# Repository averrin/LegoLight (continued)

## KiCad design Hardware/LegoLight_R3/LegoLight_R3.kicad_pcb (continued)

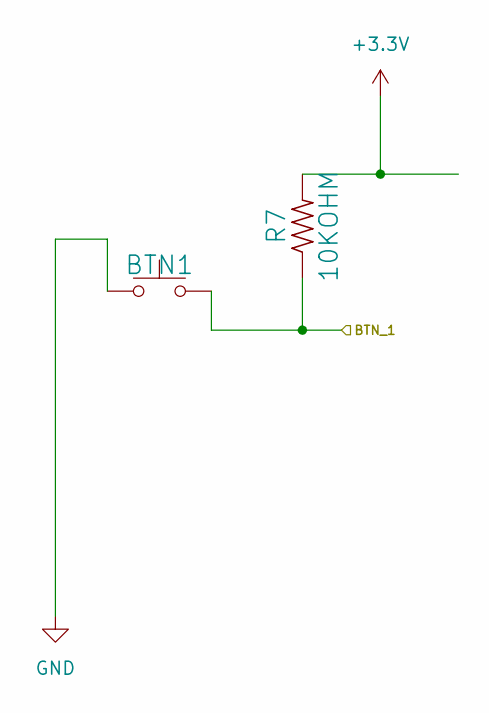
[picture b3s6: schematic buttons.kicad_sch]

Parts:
BTN1: BTN; B3U-1000P; PARTREV C; Mouser Part Number 653-B3U-1000P
R7: 10KOHM; R_0805_2012Metric_Pad1.20x1.40mm_HandSolder; Mouser Part Number 652-CR0805-JW-103ELF

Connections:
+3.3V: R7.2; also elsewhere on the board
/PA11: BTN1.2, R7.1; also elsewhere on the board
GND: BTN1.1; also elsewhere on the board

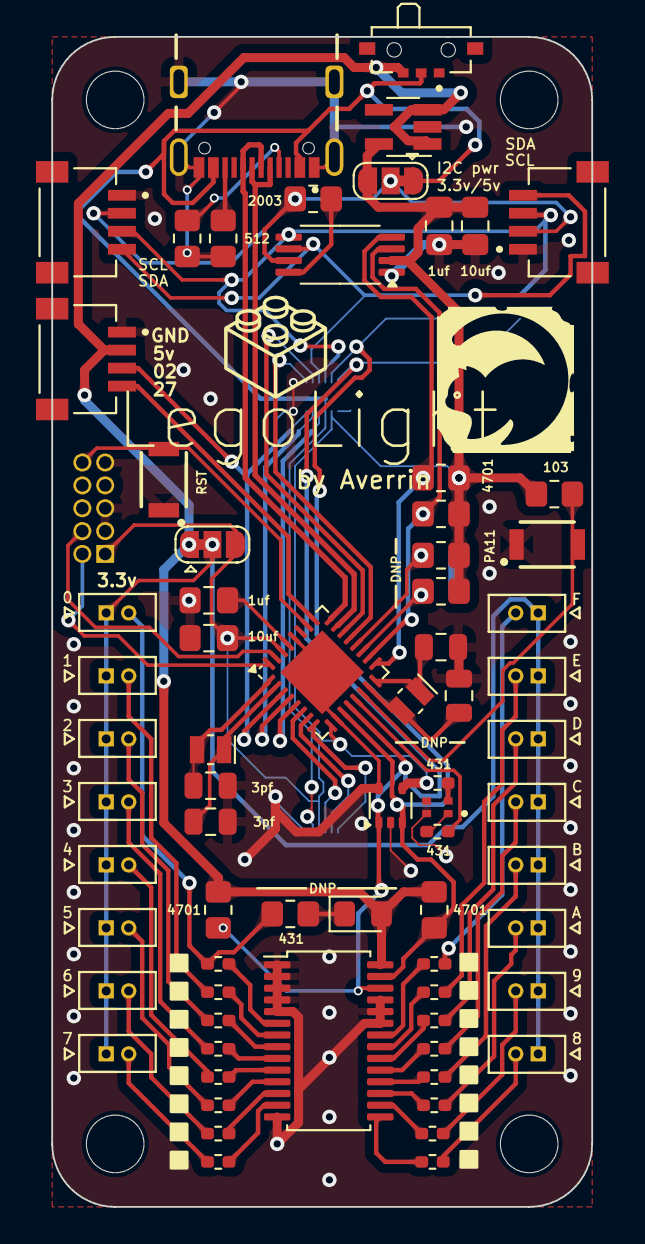
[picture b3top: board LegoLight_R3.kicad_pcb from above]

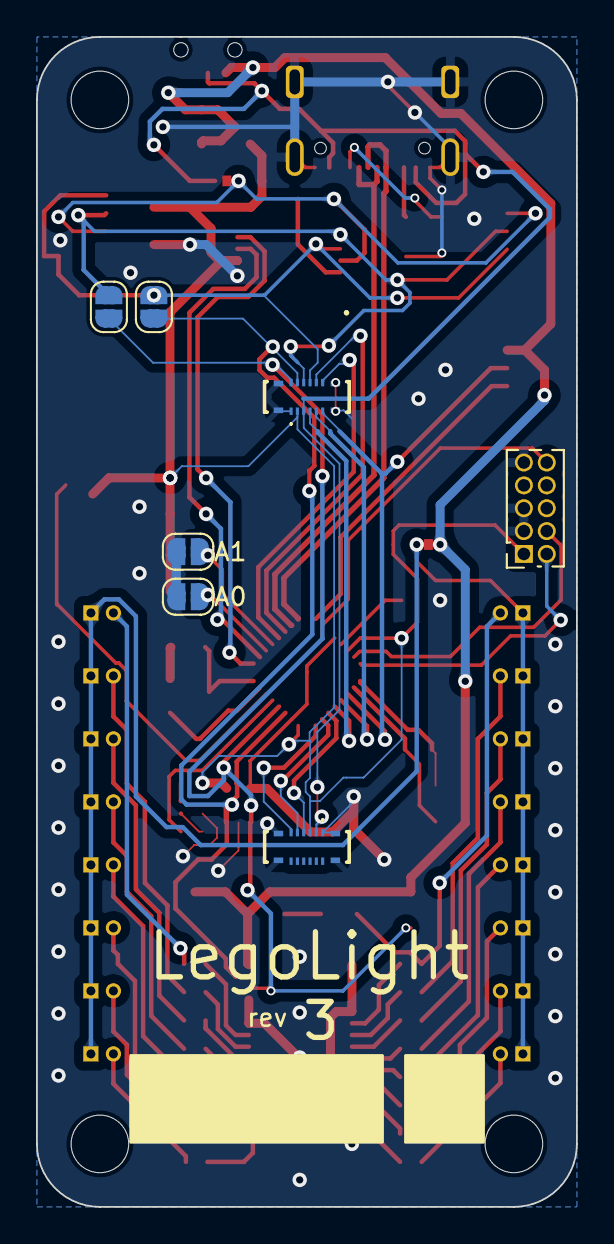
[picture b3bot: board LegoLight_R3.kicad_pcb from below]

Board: 2 copper layers, 30.0 x 65.0 mm, 82 parts (7 on the bottom side), 73 nets.

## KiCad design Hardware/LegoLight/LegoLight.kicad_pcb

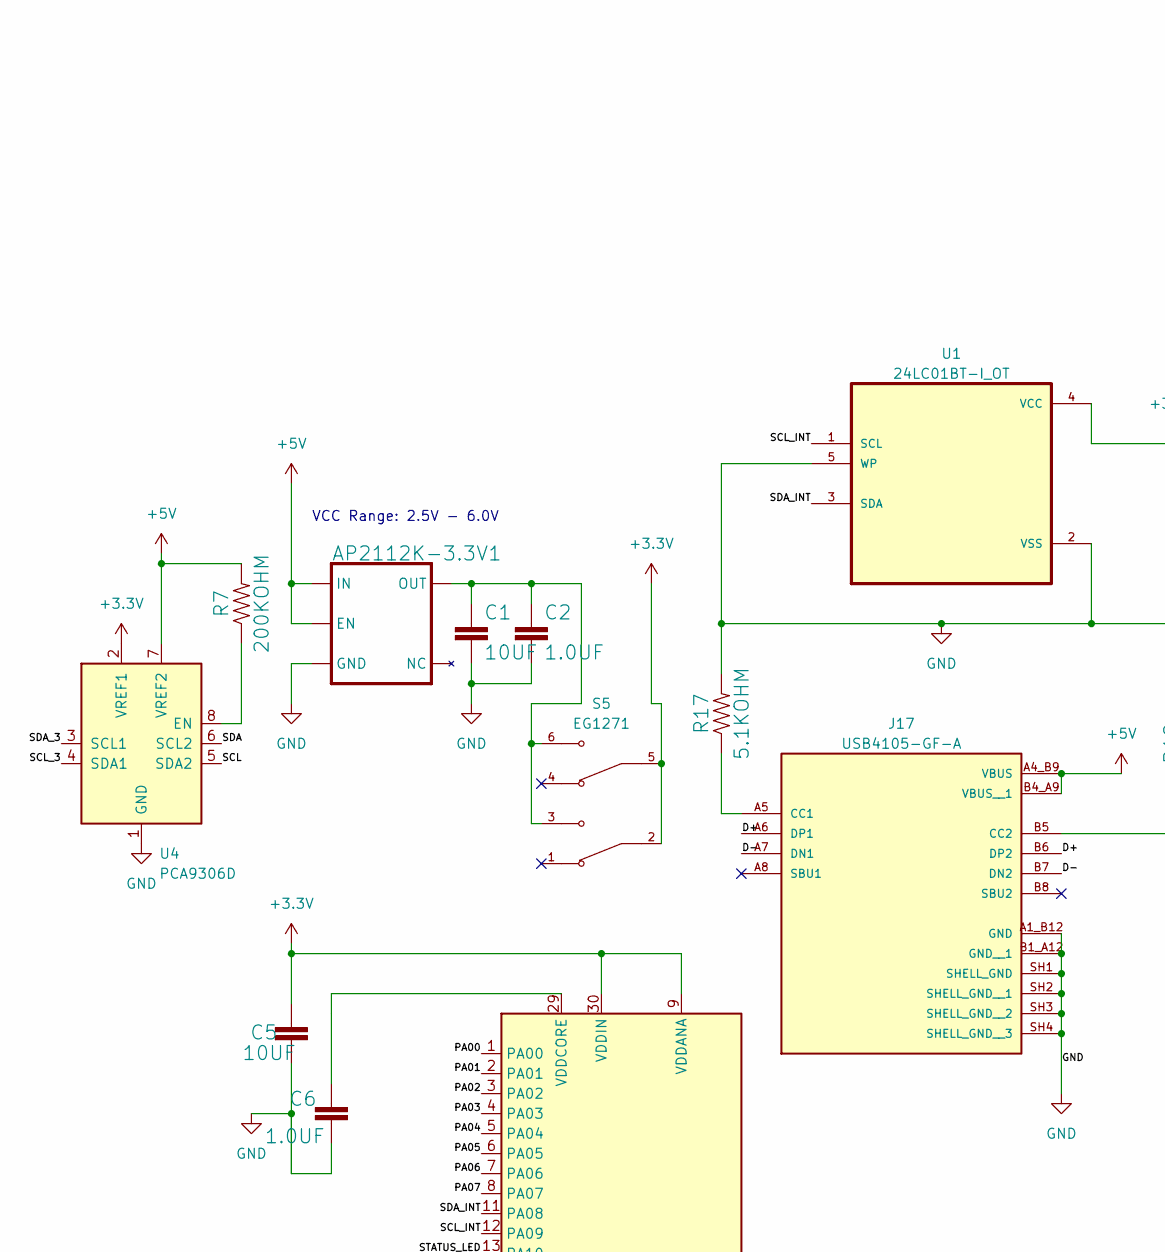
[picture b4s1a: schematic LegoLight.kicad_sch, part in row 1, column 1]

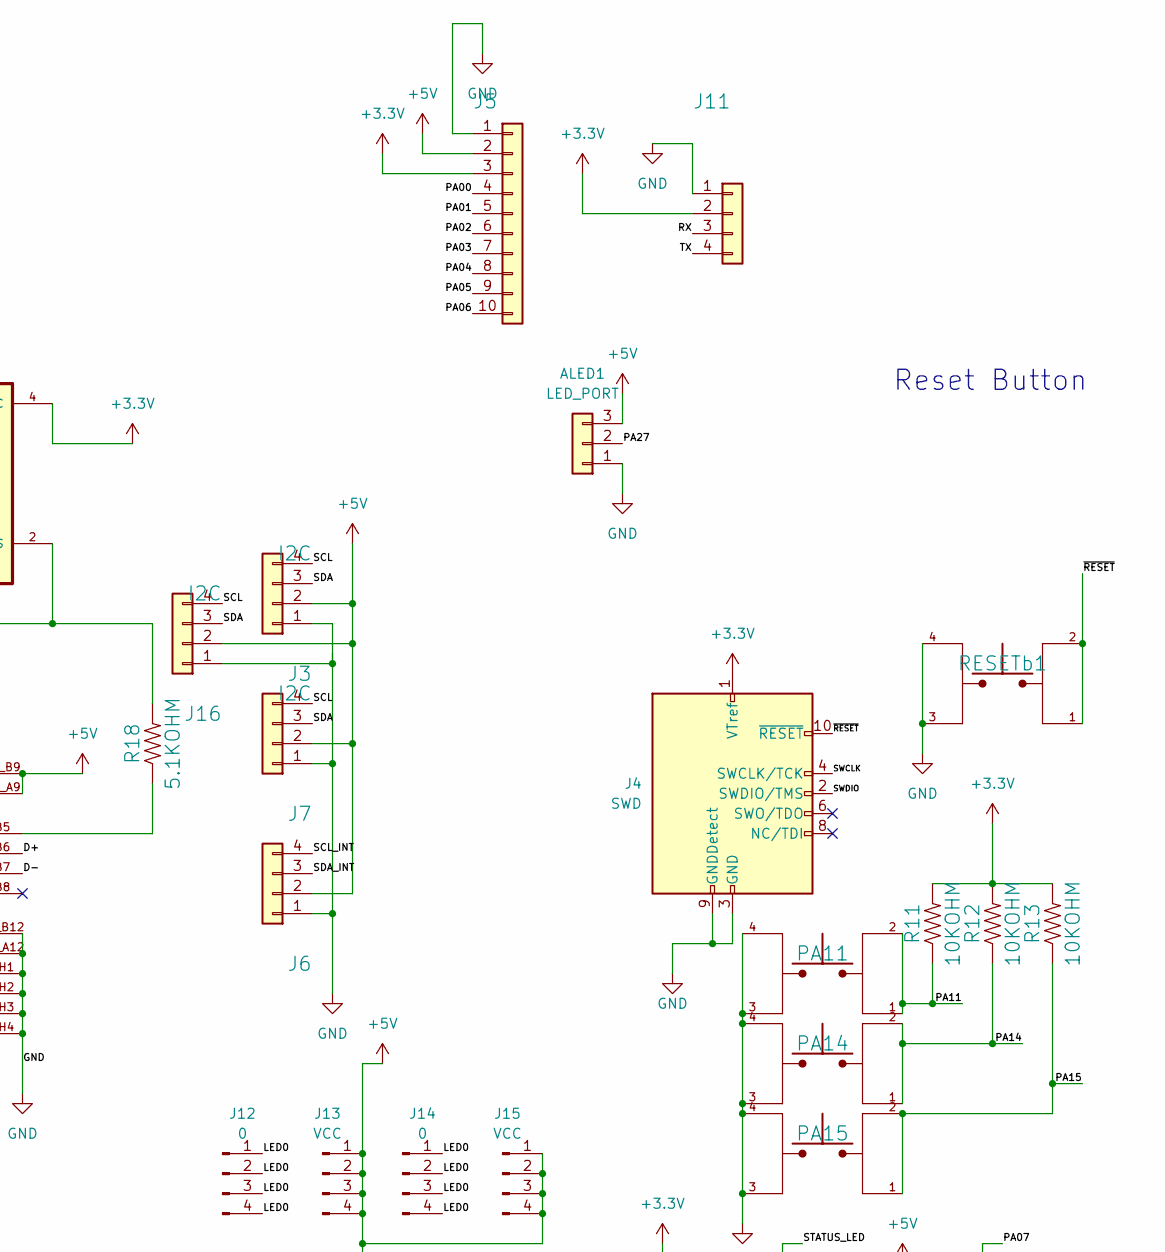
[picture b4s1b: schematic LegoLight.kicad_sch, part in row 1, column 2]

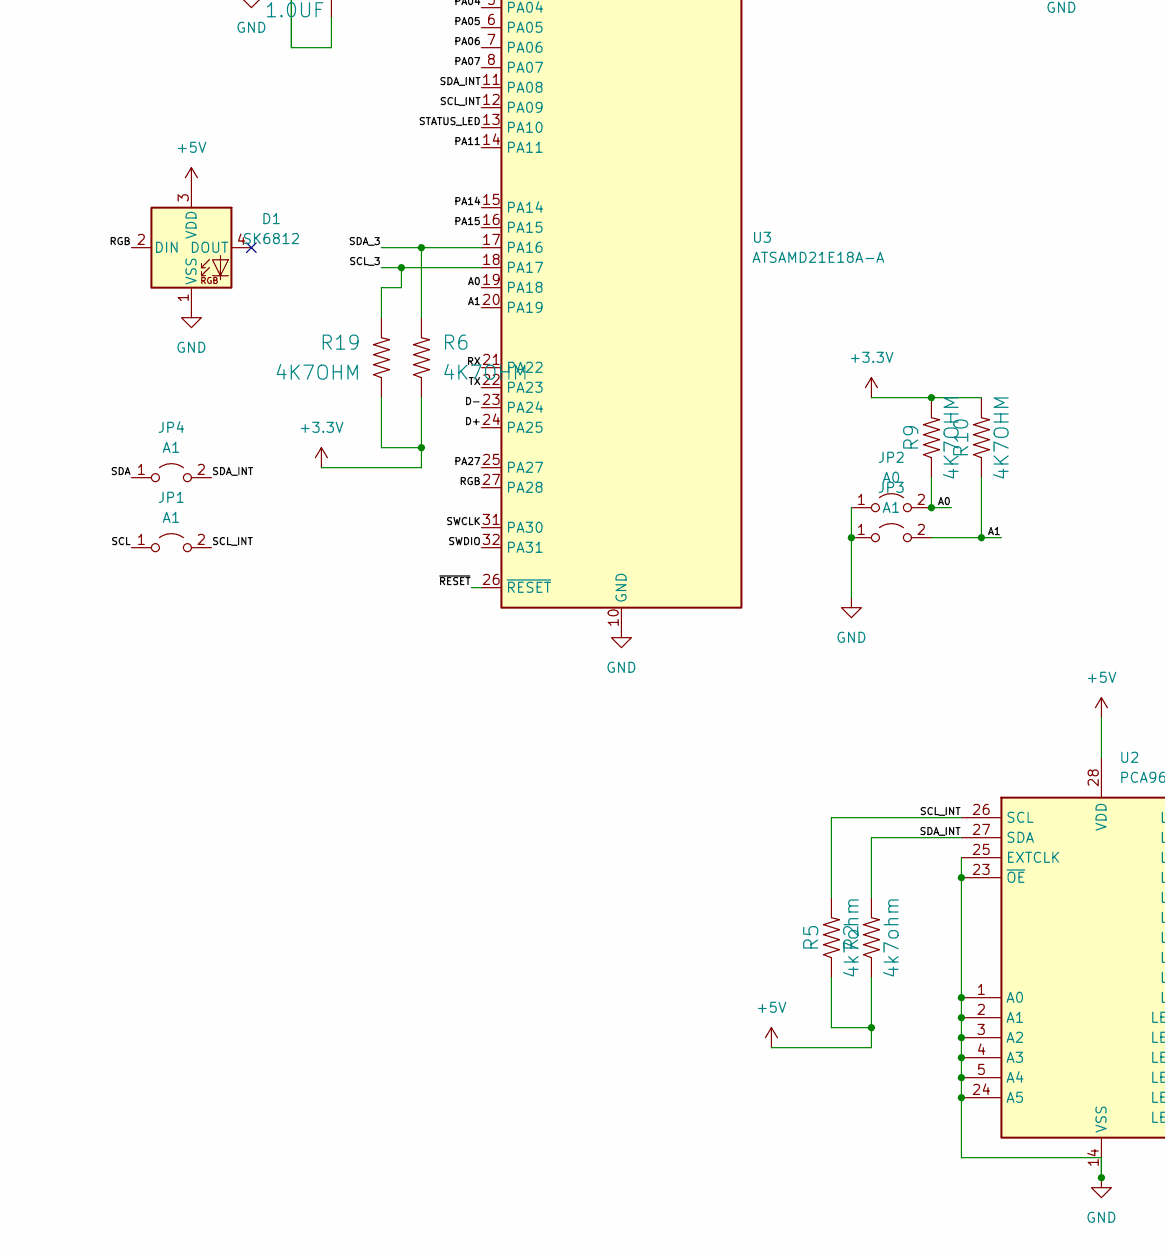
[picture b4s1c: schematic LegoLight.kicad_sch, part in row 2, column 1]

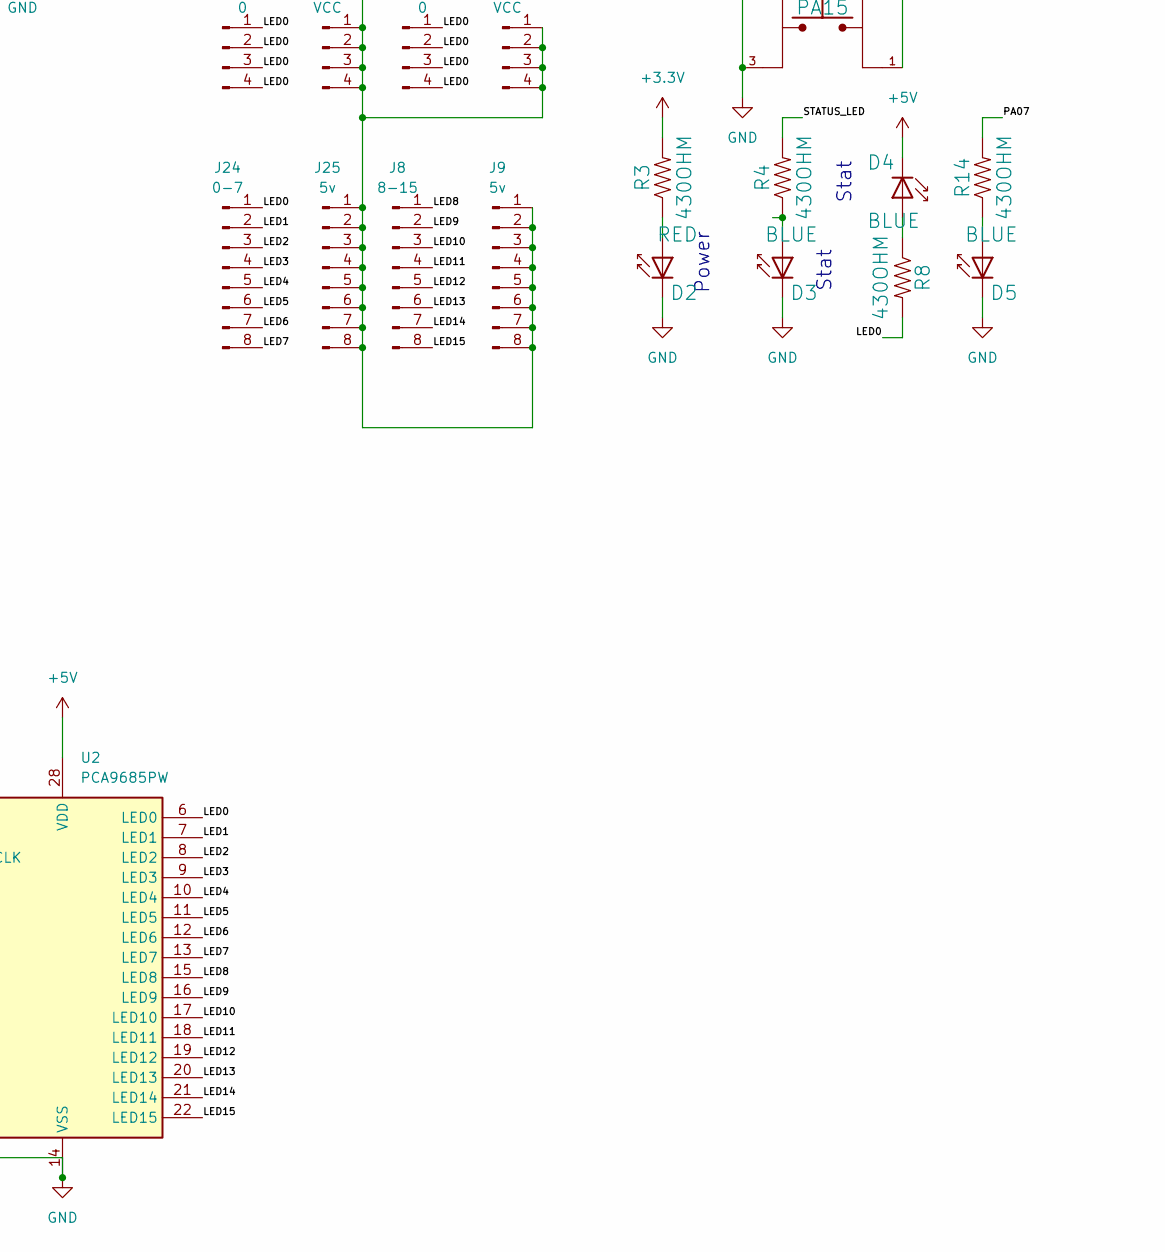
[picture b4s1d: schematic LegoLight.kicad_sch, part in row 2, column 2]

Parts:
ALED1: LED_PORT; PinHeader_1x03_P2.54mm_Vertical
AP2112K-3.3V1: AP2112K-3.3V; SOT-23-5_HandSoldering
C1, C5: 10UF; C_1206_3216Metric_Pad1.33x1.80mm_HandSolder
C2, C6: 1.0UF; C_1206_3216Metric_Pad1.33x1.80mm_HandSolder
D1: SK6812; LED_SK6812_PLCC4_5.0x5.0mm_P3.2mm
D2: RED; LED_1206_3216Metric_Pad1.42x1.75mm_HandSolder
D3, D4, D5: BLUE; LED_1206_3216Metric_Pad1.42x1.75mm_HandSolder
J3, J7: I2C; NS-Tech_Grove_1x04_P2mm_Vertical
J4: SWD; PinSocket_2x05_P1.27mm_Vertical
J5: C1; PinHeader_1x10_P2.54mm_Vertical
J6: I2C_INT; PinHeader_1x04_P2.54mm_Vertical
J8: 8-15; PinHeader_1x08_P2.54mm_Vertical
J9, J25: 5v; PinHeader_1x08_P2.54mm_Vertical
J11: C0; PinHeader_1x04_P2.54mm_Vertical
J12, J14: 0; PinHeader_1x04_P2.54mm_Vertical
J13, J15: VCC; PinHeader_1x04_P2.54mm_Vertical
J16: I2C; PinHeader_1x04_P2.54mm_Vertical
J17: USB4105-GF-A; GCT_USB4105-GF-A; PARTREV B3
J24: 0-7; PinHeader_1x08_P2.54mm_Vertical
JP1, JP3, JP4: A1; SolderJumper-2_P1.3mm_Open_RoundedPad1.0x1.5mm
JP2: A0; SolderJumper-2_P1.3mm_Open_RoundedPad1.0x1.5mm
PA11, PA14, PA15: MOMENTARY-SWITCH-SPST-SMD-4.6X2.8MM; SW_TL3305AF160QG; PARTREV C
R2, R5: 4k7ohm; R_1206_3216Metric_Pad1.30x1.75mm_HandSolder
R3, R4, R8, R14: 430OHM; R_1206_3216Metric_Pad1.30x1.75mm_HandSolder
R6, R9, R10, R19: 4K7OHM; R_1206_3216Metric_Pad1.30x1.75mm_HandSolder
R7: 200KOHM; R_1206_3216Metric_Pad1.30x1.75mm_HandSolder
R11, R12, R13: 10KOHM; R_1206_3216Metric_Pad1.30x1.75mm_HandSolder
R17, R18: 5.1KOHM; R_1206_3216Metric_Pad1.30x1.75mm_HandSolder
RESETb1: TL3305AF160QG; SW_TL3305AF160QG; PARTREV C
S5: EG1271; SW_EG1271; PARTREV G
U1: 24LC01BT-I_OT; SOT95P280X145-5N
U2: PCA9685PW; TSSOP-28_4.4x9.7mm_P0.65mm
U3: ATSAMD21E18A-A; TQFP-32_7x7mm_P0.8mm
U4: PCA9306D; SO-8_3.9x4.9mm_P1.27mm

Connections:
+3.3V: C5.1, J4.1 (VTref), J5.3, J11.2, R3.2, R6.1, R9.2, R10.2, R11.2, R12.2, R13.2, R19.1, S5.2, S5.5, U1.4 (VCC), U3.9 (VDDANA), U3.30 (VDDIN), U4.2 (VREF1)
+5V: ALED1.3, AP2112K-3.3V1.1 (IN), AP2112K-3.3V1.3 (EN), D1.3 (VDD), D4.1 (K), J3.2, J5.2, J6.2, J7.2, J9.1, J9.2, J9.3, J9.4, J9.5, J9.6, J9.7, J9.8, J13.1, J13.2, J13.3, J13.4, J15.1, J15.2, J15.3, J15.4, J16.2, J17.A4_B9 (VBUS), J17.B4_A9 (VBUS__1), J25.1, J25.2, J25.3, J25.4, J25.5, J25.6, J25.7, J25.8, R2.1, R5.1, R7.2, U2.28 (VDD), U4.7 (VREF2)
/A0: JP2.2 (B), R9.1, U3.19 (PA18)
/A1: JP3.2 (B), R10.1, U3.20 (PA19)
/D+: J17.A6 (DP1), J17.B6 (DP2), U3.24 (PA25)
/D-: J17.A7 (DN1), J17.B7 (DN2), U3.23 (PA24)
/LED0: J12.1, J12.2, J12.3, J12.4, J14.1, J14.2, J14.3, J14.4, J24.1, R8.2, U2.6 (LED0)
/LED1: J24.2, U2.7 (LED1)
/LED2: J24.3, U2.8 (LED2)
/LED3: J24.4, U2.9 (LED3)
/LED4: J24.5, U2.10 (LED4)
/LED5: J24.6, U2.11 (LED5)
/LED6: J24.7, U2.12 (LED6)
/LED7: J24.8, U2.13 (LED7)
/LED8: J8.1, U2.15 (LED8)
/LED9: J8.2, U2.16 (LED9)
/LED10: J8.3, U2.17 (LED10)
/LED11: J8.4, U2.18 (LED11)
/LED12: J8.5, U2.19 (LED12)
/LED13: J8.6, U2.20 (LED13)
/LED14: J8.7, U2.21 (LED14)
/LED15: J8.8, U2.22 (LED15)
/PA00: J5.4, U3.1 (PA00)
/PA01: J5.5, U3.2 (PA01)
/PA02: J5.6, U3.3 (PA02)
/PA03: J5.7, U3.4 (PA03)
/PA04: J5.8, U3.5 (PA04)
/PA05: J5.9, U3.6 (PA05)
/PA06: J5.10, U3.7 (PA06)
/PA07: R14.2, U3.8 (PA07)
/PA11: PA11.1, PA11.2, R11.1, U3.14 (PA11)
/PA14: PA14.1, PA14.2, R12.1, U3.15 (PA14)
/PA15: PA15.1, PA15.2, R13.1, U3.16 (PA15)
/PA27: ALED1.2, U3.25 (PA27)
/RGB: D1.2 (DIN), U3.27 (PA28)
/RX: J11.3, U3.21 (PA22)
/SCL: J3.4, J7.4, J16.4, JP1.1 (A), U4.5 (SDA2)
/SCL_3: R19.2, U3.18 (PA17), U4.4 (SDA1)
/SCL_INT: J6.4, JP1.2 (B), R5.2, U1.1 (SCL), U2.26 (SCL), U3.12 (PA09)
/SDA: J3.3, J7.3, J16.3, JP4.1 (A), U4.6 (SCL2)
/SDA_3: R6.2, U3.17 (PA16), U4.3 (SCL1)
/SDA_INT: J6.3, JP4.2 (B), R2.2, U1.3 (SDA), U2.27 (SDA), U3.11 (PA08)
/STATUS_LED: R4.2, U3.13 (PA10)
/SWCLK: J4.4 (SWCLK/TCK), U3.31 (PA30)
/SWDIO: J4.2 (SWDIO/TMS), U3.32 (PA31)
/TX: J11.4, U3.22 (PA23)
/~RESET: J4.10 (~RESET), RESETb1.1, RESETb1.2, U3.26 (~RESET)
GND: ALED1.1, AP2112K-3.3V1.2 (GND), C1.2, C2.2, C5.2, C6.1, D1.1 (VSS), D2.1 (K), D3.1 (K), D5.1 (K), J3.1, J4.3 (GND), J4.5 (GND), J4.9 (GNDDetect), J5.1, J6.1, J7.1, J11.1, J16.1, J17.A1_B12 (GND), J17.B1_A12 (GND__1), J17.SH1 (SHELL_GND), J17.SH2 (SHELL_GND__1), J17.SH3 (SHELL_GND__2), J17.SH4 (SHELL_GND__3), JP2.1 (A), JP3.1 (A), PA11.3, PA11.4, PA14.3, PA14.4, PA15.3, PA15.4, R17.2, R18.2, RESETb1.3, RESETb1.4, U1.2 (VSS), U1.5 (WP), U2.1 (A0), U2.2 (A1), U2.3 (A2), U2.4 (A3), U2.5 (A4), U2.14 (VSS), U2.23 (~OE), U2.24 (A5), U2.25 (EXTCLK), U3.10 (GND), U3.28 (GND), U4.1 (GND)
unnamed: AP2112K-3.3V1.5 (OUT), C1.1, C2.1, S5.3, S5.6
unnamed: D2.2 (A), R3.1
unnamed: D3.2 (A), R4.1
unnamed: D4.2 (A), R8.1
unnamed: D5.2 (A), R14.1
unnamed: J17.A5 (CC1), R17.1
unnamed: J17.B5 (CC2), R18.1
unnamed: C6.2, U3.29 (VDDCORE)
unnamed: R7.1, U4.8 (EN)

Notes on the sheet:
Power
Stat
Reset Button
VCC Range: 2.5V - 6.0V

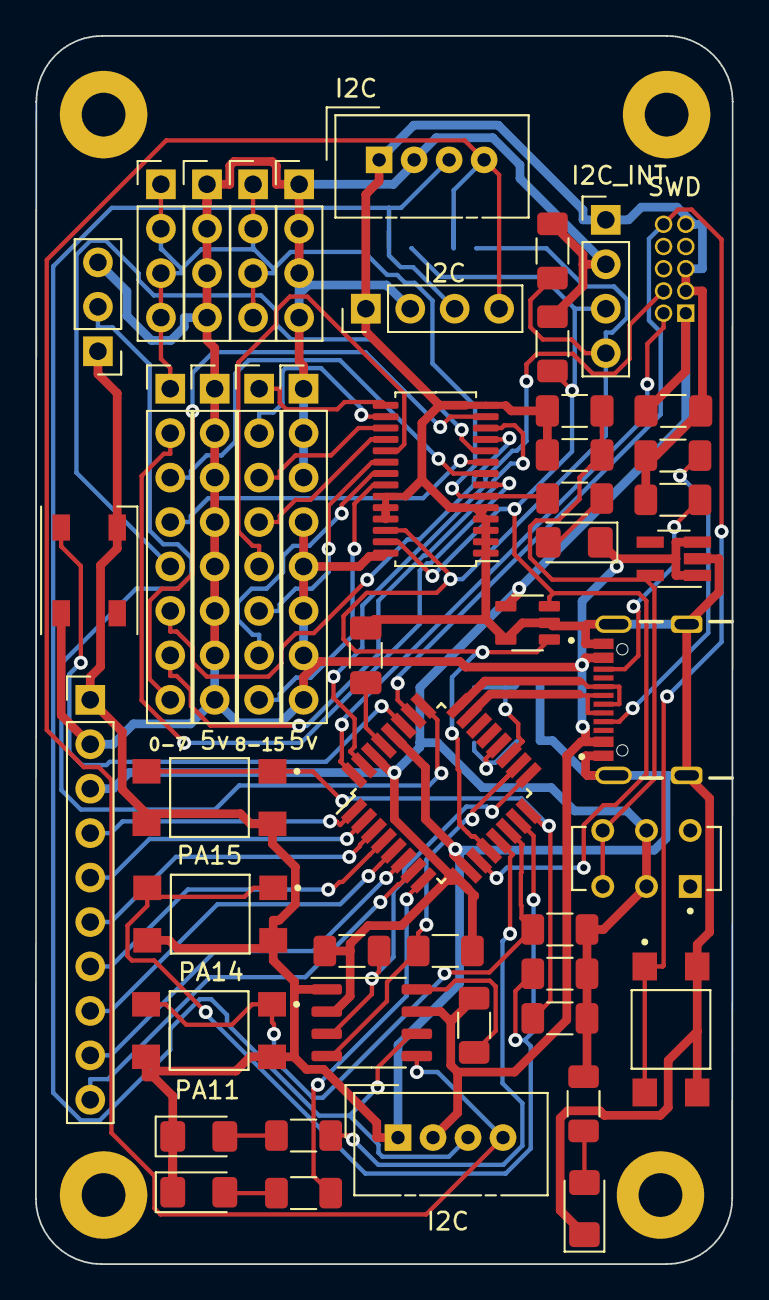
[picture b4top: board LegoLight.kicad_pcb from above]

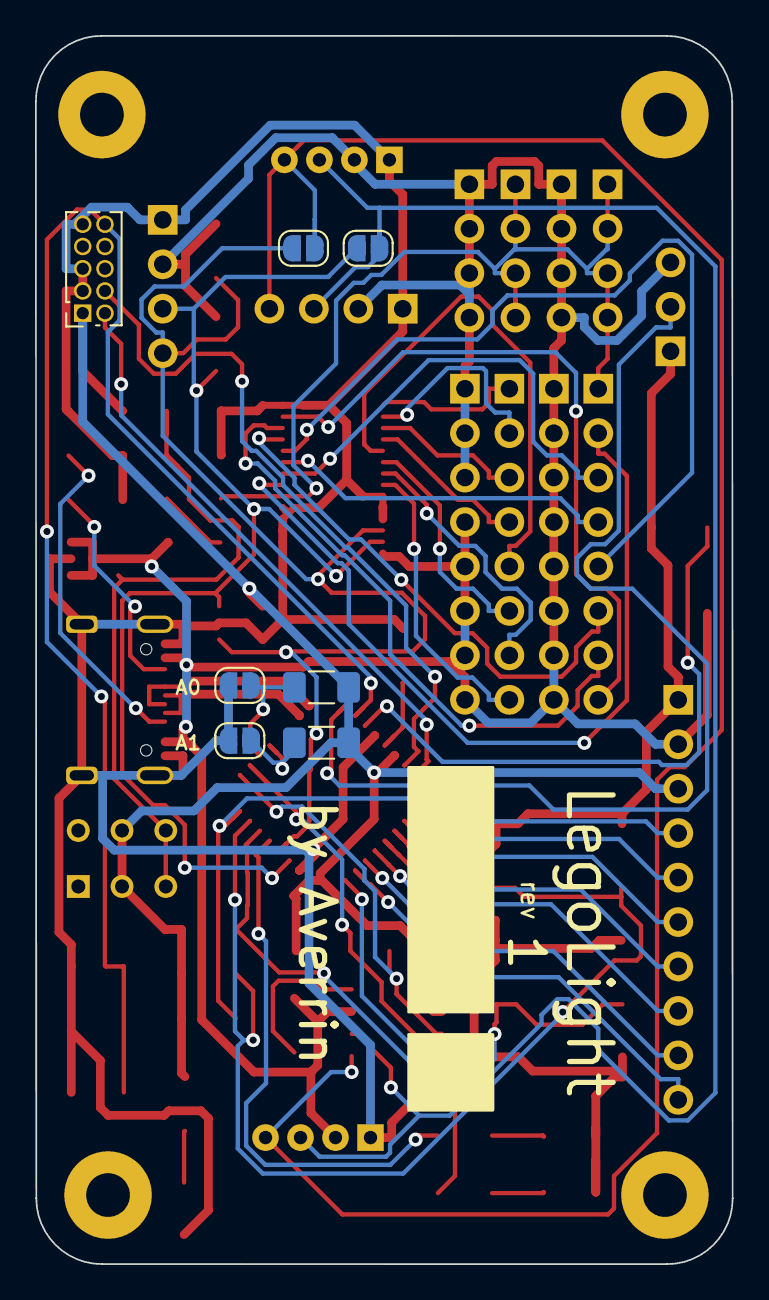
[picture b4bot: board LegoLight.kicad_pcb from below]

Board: 2 copper layers, 39.8 x 70.2 mm, 59 parts (7 on the bottom side), 55 nets.

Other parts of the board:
MH1, MH2, MH3, MH4: MountingHole_2.5mm_Pad

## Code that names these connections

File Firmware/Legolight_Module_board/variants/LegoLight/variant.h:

/*
  Copyright (c) 2014-2015 Arduino LLC.  All right reserved.

  This library is free software; you can redistribute it and/or
  modify it under the terms of the GNU Lesser General Public
  License as published by the Free Software Foundation; either
  version 2.1 of the License, or (at your option) any later version.

  This library is distributed in the hope that it will be useful,
  but WITHOUT ANY WARRANTY; without even the implied warranty of
  MERCHANTABILITY or FITNESS FOR A PARTICULAR PURPOSE.
  See the GNU Lesser General Public License for more details.

  You should have received a copy of the GNU Lesser General Public
  License along with this library; if not, write to the Free Software
  Foundation, Inc., 51 Franklin St, Fifth Floor, Boston, MA  02110-1301  USA
*/

#ifndef _VARIANT_ARDUINO_ZERO_
#define _VARIANT_ARDUINO_ZERO_

// The definitions here needs a SAMD core >=1.6.6
#define ARDUINO_SAMD_VARIANT_COMPLIANCE 10606

/*----------------------------------------------------------------------------
 *        Definitions
 *----------------------------------------------------------------------------*/

/** Frequency of the board main oscillator */
#define VARIANT_MAINOSC (32768ul)

/** Master clock frequency */
#define VARIANT_MCK (F_CPU)

/*----------------------------------------------------------------------------
 *        Headers
 *----------------------------------------------------------------------------*/

#include "WVariant.h"

#ifdef __cplusplus
#include "SERCOM.h"
#include "Uart.h"
#endif // __cplusplus

#ifdef __cplusplus
extern "C"
{
#endif // __cplusplus

/*----------------------------------------------------------------------------
 *        Pins
 *----------------------------------------------------------------------------*/

// Number of pins defined in PinDescription array
#define PINS_COUNT (36u)
#define NUM_DIGITAL_PINS (30u)
#define NUM_ANALOG_INPUTS (6u)
#define NUM_ANALOG_OUTPUTS (1u)
#define analogInputToDigitalPin(p) ((p < 6u) ? (p) + 22u : -1)

#define digitalPinToPort(P) (&(PORT->Group[g_APinDescription[P].ulPort]))
#define digitalPinToBitMask(P) (1 << g_APinDescription[P].ulPin)
// #define analogInPinToBit(P)        ( )
#define portOutputRegister(port) (&(port->OUT.reg))
#define portInputRegister(port) (&(port->IN.reg))
#define portModeRegister(port) (&(port->DIR.reg))
#define digitalPinHasPWM(P) (g_APinDescription[P].ulPWMChannel != NOT_ON_PWM || g_APinDescription[P].ulTCChannel != NOT_ON_TIMER)

/*
 * digitalPinToTimer(..) is AVR-specific and is not defined for SAMD
 * architecture. If you need to check if a pin supports PWM you must
 * use digitalPinHasPWM(..).
 *
 * https://github.com/arduino/Arduino/issues/1833
 */
// #define digitalPinToTimer(P)

// RX and TX LEDs are not present on the board.
#define PIN_LED_13 (13u)
// #define PIN_LED_RXL (25u)
// #define PIN_LED_TXL (26u)
#define PIN_LED PIN_LED_13
// #define PIN_LED2 PIN_LED_RXL
// #define PIN_LED3 PIN_LED_TXL
#define LED_BUILTIN PIN_LED_13

/*
 * Analog pins
 */
#define PIN_A0 (24u)
#define PIN_A1 (PIN_A0 + 1)
#define PIN_A2 (PIN_A0 + 2)
#define PIN_A3 (PIN_A0 + 3)
#define PIN_A4 (PIN_A0 + 4)
#define PIN_A5 (PIN_A0 + 5)
#define PIN_DAC0 PIN_A0

  static const uint8_t A0 = PIN_A0;
  static const uint8_t A1 = PIN_A1;
  static const uint8_t A2 = PIN_A2;
  static const uint8_t A3 = PIN_A3;
  static const uint8_t A4 = PIN_A4;
  static const uint8_t A5 = PIN_A5;
  static const uint8_t DAC0 = PIN_DAC0;
#define ADC_RESOLUTION 12

/*
 * Serial interfaces
 */

// Serial
// #define PIN_SERIAL_TX (16ul)
// #define PIN_SERIAL_RX (17ul)
// #define PAD_SERIAL_TX (UART_TX_PAD_0)
// #define PAD_SERIAL_RX (SERCOM_RX_PAD_1)

/*
 * SPI Interfaces
 */
#define SPI_INTERFACES_COUNT 1

#define PIN_SPI_MOSI (14u)
#define PIN_SPI_MISO (15u)
#define PIN_SPI_SCK (11u)
#define PIN_SPI_SS (7u)
#define PERIPH_SPI sercom0
#define PAD_SPI_TX SPI_PAD_2_SCK_3
#define PAD_SPI_RX SERCOM_RX_PAD_1

  static const uint8_t SS = PIN_SPI_SS;
  static const uint8_t MOSI = PIN_SPI_MOSI;
  static const uint8_t MISO = PIN_SPI_MISO;
  static const uint8_t SCK = PIN_SPI_SCK;

// #define PIN_SPI1_MOSI (18u)
// #define PIN_SPI1_SCK (19u)
// #define PIN_SPI1_MISO (20u)
// #define PIN_SPI1_SS (21u)
// #define PERIPH_SPI1 sercom1
// #define PAD_SPI1_TX SPI_PAD_0_SCK_1
// #define PAD_SPI1_RX SERCOM_RX_PAD_2

//   static const uint8_t FLASH_SS = PIN_SPI1_SS;
//   static const uint8_t FLASH_MOSI = PIN_SPI1_MOSI;
//   static const uint8_t FLASH_MISO = PIN_SPI1_MISO;
//   static const uint8_t FLASH_SCK = PIN_SPI1_SCK;

/*
 * Wire Interfaces
 */
// I2C/Qwiic Interface
#define WIRE_INTERFACES_COUNT 2

#define PIN_WIRE_SDA (9u)
#define PIN_WIRE_SCL (10u)
#define PERIPH_WIRE sercom2
#define WIRE_IT_HANDLER SERCOM2_Handler

  static const uint8_t SDA = PIN_WIRE_SDA;
  static const uint8_t SCL = PIN_WIRE_SCL;

#define PIN_WIRE1_SDA (18u)
#define PIN_WIRE1_SCL (19u)
#define PERIPH_WIRE1 sercom1
#define WIRE1_IT_HANDLER SERCOM1_Handler
/*
 * USB
 */
#define PIN_USB_HOST_ENABLE (30ul)
#define PIN_USB_DM (31ul)
#define PIN_USB_DP (32ul)

#ifdef __cplusplus
}
#endif

/*----------------------------------------------------------------------------
 *        Arduino objects - C++ only
 *----------------------------------------------------------------------------*/

#ifdef __cplusplus

/*	=========================
 *	===== SERCOM DEFINITION
 *	=========================
 */
extern SERCOM sercom0;
extern SERCOM sercom1;
extern SERCOM sercom2;
extern SERCOM sercom3;

extern Uart Serial;

#endif

// These serial port names are intended to allow libraries and architecture-neutral
// sketches to automatically default to the correct port name for a particular type
// of use.  For example, a GPS module would normally connect to SERIAL_PORT_HARDWARE_OPEN,
// the first hardware serial port whose RX/TX pins are not dedicated to another use.
//
// SERIAL_PORT_MONITOR        Port which normally prints to the Arduino Serial Monitor
//
// SERIAL_PORT_USBVIRTUAL     Port which is USB virtual serial
//
// SERIAL_PORT_LINUXBRIDGE    Port which connects to a Linux system via Bridge library
//
// SERIAL_PORT_HARDWARE       Hardware serial port, physical RX & TX pins.
//
// SERIAL_PORT_HARDWARE_OPEN  Hardware serial ports which are open for use.  Their RX & TX
//                            pins are NOT connected to anything by default.
#define SERIAL_PORT_USBVIRTUAL SerialUSB
#define SERIAL_PORT_MONITOR SerialUSB
// #define SERIAL_PORT_HARDWARE Serial
// #define SERIAL_PORT_HARDWARE_OPEN Serial

#define PIN_PA11 (33u)
#define PIN_PA14 (34u)
#define PIN_PA15 (35u)
#define PIN_PA18 (20u)
#define PIN_PA19 (21u)

#define PIN_PA16 (18u)
#define PIN_PA17 (19u)
#define PIN_PA27 (36u)
#define PIN_PA28 (30u)

#endif /* _VARIANT_ARDUINO_ZERO_ */

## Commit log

2024-04-14 init hardware
2024-04-19 upload firmware
2024-04-19 deevice indication
2024-04-20 add board files
2024-04-21 hq pcb
2024-05-05 update pcbs
2024-05-05 add hq header to solo
2024-05-11 final?
2024-05-12 add r2 enclosure
2024-05-12 update case
